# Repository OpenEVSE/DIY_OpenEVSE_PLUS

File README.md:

# DIY_OpenEVSE_PLUS
Do it Yourself through hole boards

Do it yourself boards are for expert builders, no offical support is provided.

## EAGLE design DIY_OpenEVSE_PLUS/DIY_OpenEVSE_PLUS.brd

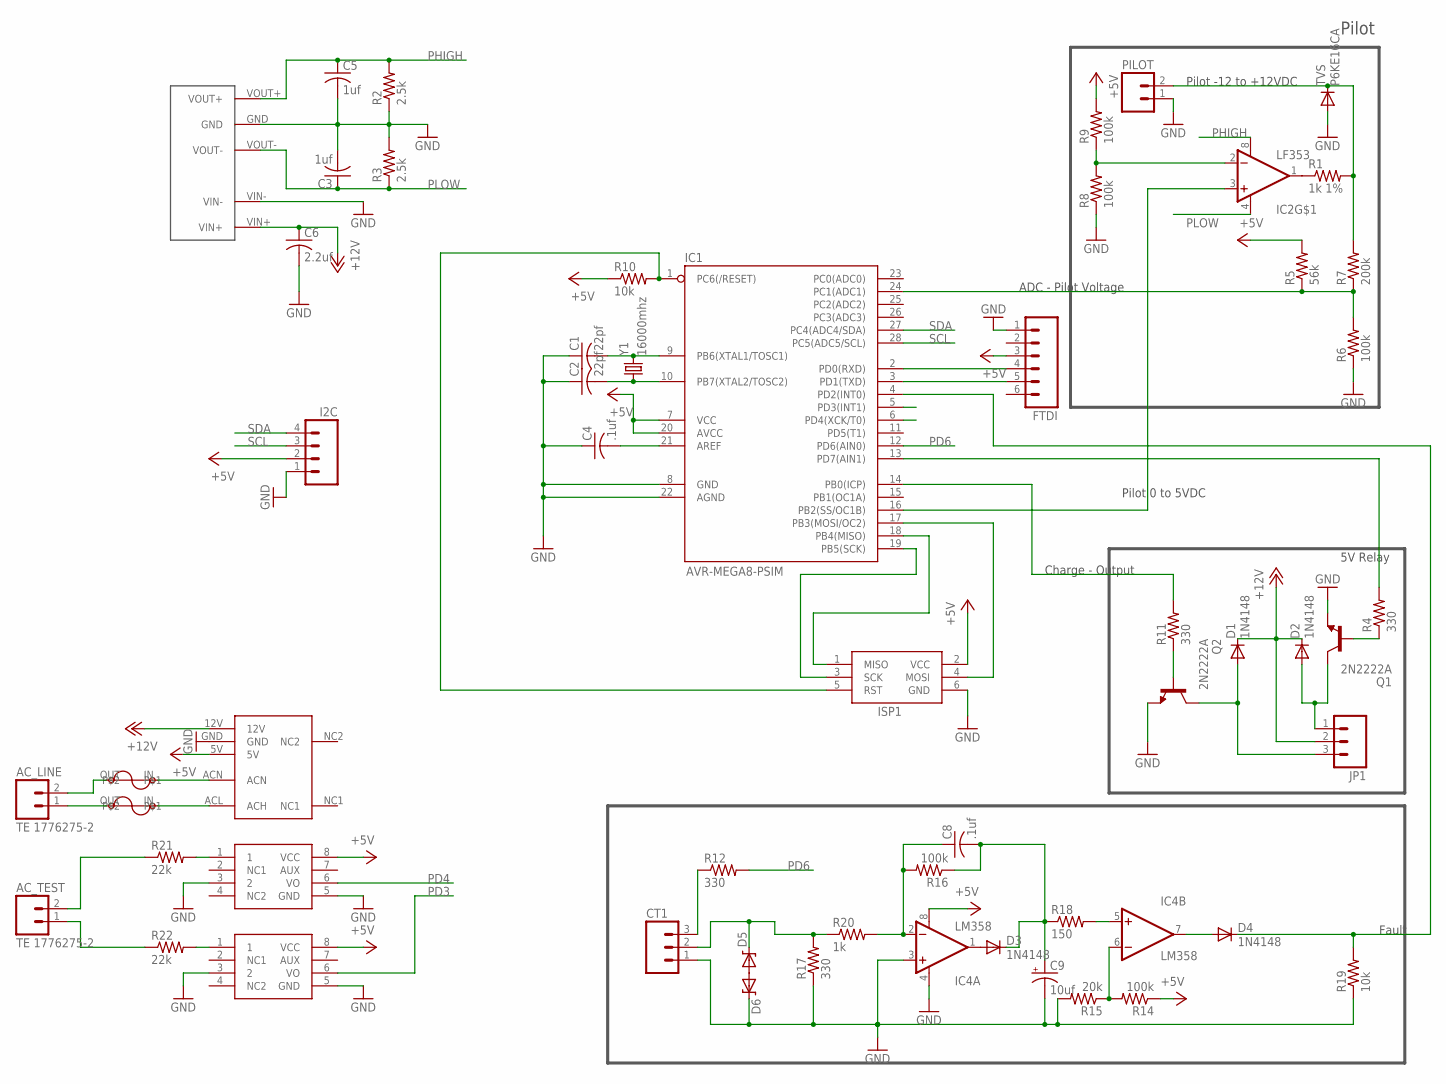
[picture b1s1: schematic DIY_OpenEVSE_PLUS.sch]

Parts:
AC_LINE: TE 1776275-2; SCREWTERMINAL-3.5MM-2_LOCK
AC_TEST: TE 1776275-2; SCREWTERMINAL-3.5MM-2_LOCK
C1, C2: 22pf; C025-024X044
C3, C5: 1uf; C025-024X044
C4, C8: .1uf; C025-024X044
C6: 2.2uf; C025-024X044
C9: 10uf; CPOL-RADIAL-10UF-25V
CT1: M03LOCK; 1X03_LOCK
D1, D2, D3, D4: 1N4148; DIODE-1N4148
D5, D6: DIODE-ZENERPTH; DIODE-ZENER
DCDC: D107E; DCDC_SIP
FTDI: M06LOCK; 1X06_LOCK
I2C: M04LOCK; 1X04_LOCK
IC1: AVR-MEGA8-PSIM; DIL28-3-SIMON
IC2: LF353; DIP08
IC3, IC5: MID400; DIP08
IC4: LM358; DIP08
ISP1: AVRISP-6; AVRISP
JP1: M03SCREW_LOCK; SCREWTERMINAL-3.5MM-3_LOCK.007S
PILOT: M025MM; SCREWTERMINAL-5MM-2
Q1, Q2: 2N2222A; TO18
R1: 1k 1%; 0204/7
R2, R3: 2.5k; 0204/7
R4, R11, R12, R17: 330; 0204/7
R5: 56k; 0204/7
R6, R8, R9, R14, R16: 100k; 0204/7
R7: 200k; 0204/7
R10, R19: 10k; 0204/7
R15: 20k; 0204/7
R18: 150; 0204/7
R20: 1k; 0204/7
R21, R22: 22k; AXIAL-0.4
TVS: P6KE16CA; DIODE-1N4001
U$3, U$5: BEL1AFUSE; BELFUSE1A
U$4: MPM-04E-1205
Y1: 16000mhz; HC49U-V

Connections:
+5V: FTDI.3, I2C.2, IC1.7 (VCC), IC1.20 (AVCC), IC3.8 (VCC), IC4.8 (V+), IC5.8 (VCC), ISP1.2 (VCC), R5.2, R9.2, R10.1, R14.1, U$4.5V
+12V: C6.1, D1.C, D2.C, DCDC.VIN+, JP1.2, U$4.12V
GND: C1.1, C2.1, C3.2, C4.1, C5.2, C6.2, C9.2 (-), CT1.1, D6.P$1 (C), DCDC.GND, DCDC.VIN-, FTDI.1, I2C.1, IC1.8 (GND), IC1.22 (AGND), IC3.3 (2), IC3.5 (GND), IC4.3 (+IN), IC4.4 (V-), IC5.3 (2), IC5.5 (GND), ISP1.6 (GND), PILOT.1, Q1.1 (E), Q2.1 (E), R2.1, R3.2, R6.1, R8.1, R15.2, R17.1, R19.1, TVS.A, U$4.GND
unnamed: AC_LINE.1, U$3.OUT
unnamed: Q2.2 (B), R11.1
unnamed: PILOT.2, R1.2, R7.2, TVS.C
unnamed: C1.2, IC1.9 (PB6(XTAL1/TOSC1)), Y1.2
unnamed: C2.2, IC1.10 (PB7(XTAL2/TOSC2)), Y1.1
unnamed: AC_LINE.2, U$5.OUT
unnamed: C4.2, IC1.21 (AREF)
unnamed: FTDI.5, IC1.3 (PD1(TXD))
unnamed: IC3.1, R21.P$2 (2)
unnamed: IC2.2 (-IN), R8.2, R9.1
unnamed: IC2.1 (OUT), R1.1
unnamed: FTDI.4, IC1.2 (PD0(RXD))
unnamed: D1.A, JP1.3, Q2.3 (C)
unnamed: IC1.17 (PB3(MOSI/OC2)), ISP1.4 (MOSI)
unnamed: IC1.19 (PB5(SCK)), ISP1.3 (SCK)
unnamed: IC1.18 (PB4(MISO)), ISP1.1 (MISO)
unnamed: IC5.1, R22.P$2 (2)
unnamed: C8.1, IC4.2 (-IN), R16.2, R20.2
unnamed: IC4.5 (+IN), R18.2
unnamed: CT1.2, D5.P$1 (C), R17.2, R20.1
unnamed: D3.A, IC4.1 (OUT)
unnamed: D5.P$2 (A), D6.P$2 (A)
unnamed: C8.2, C9.1 (+), D3.C, R16.1, R18.1
unnamed: IC4.6 (-IN), R14.2, R15.1
unnamed: D4.A, IC4.7 (OUT)
unnamed: AC_TEST.2, R21.P$1 (1)
unnamed: U$3.IN, U$4.ACL (ACH)
unnamed: D4.C, IC1.4 (PD2(INT0)), R19.2
unnamed: AC_TEST.1, R22.P$1 (1)
unnamed: U$4.ACN, U$5.IN
unnamed: Q1.2 (B), R4.1
unnamed: D2.A, JP1.1, Q1.3 (C)
unnamed: IC1.13 (PD7(AIN1)), R4.2
unnamed: IC1.14 (PB0(ICP)), R11.2
unnamed: CT1.3, R12.1
unnamed: IC1.24 (PC1(ADC1)), R5.1, R6.2, R7.1
PD3: IC1.5 (PD3(INT1)), IC5.6 (VO)
PD4: IC1.6 (PD4(XCK/T0)), IC3.6 (VO)
PD6: IC1.12 (PD6(AIN0)), R12.2
PHIGH: C5.1, DCDC.VOUT+, IC2.8 (V+), R2.2
PLOW: C3.1, DCDC.VOUT-, IC2.4 (V-), R3.1
RST: IC1.1 (PC6(/RESET)), ISP1.5 (RST), R10.2
S$2: IC1.16 (PB2(SS/OC1B)), IC2.3 (+IN)
SCL: I2C.3, IC1.28 (PC5(ADC5/SCL))
SDA: I2C.4, IC1.27 (PC4(ADC4/SDA))

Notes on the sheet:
Pilot
ADC - Pilot Voltage
Pilot -12 to +12VDC
Pilot 0 to 5VDC
Charge - Output
5V Relay
Fault

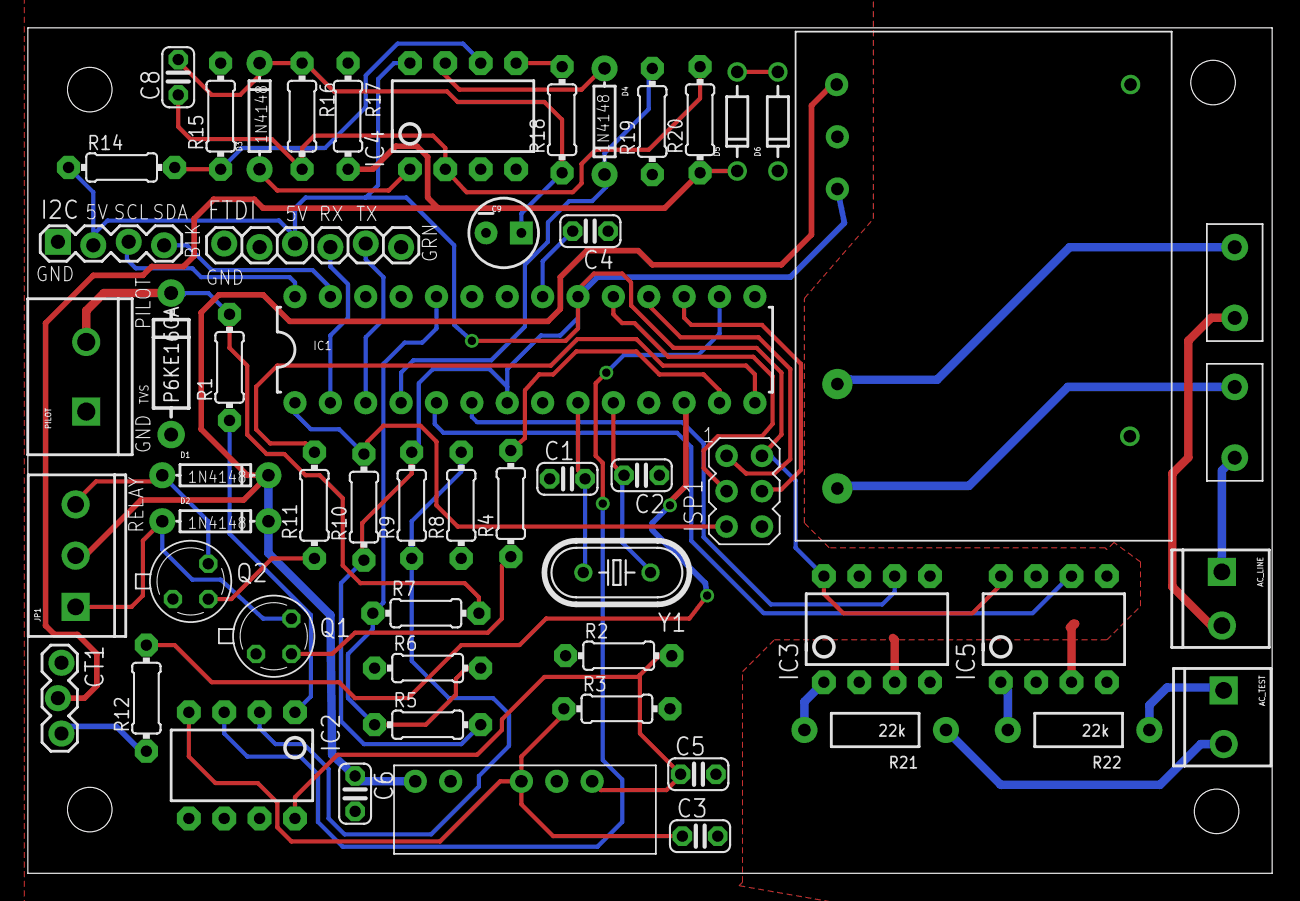
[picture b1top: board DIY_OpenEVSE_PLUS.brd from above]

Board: 2 copper layers, 89.3 x 60.7 mm, 56 parts (0 on the bottom side), 48 nets.

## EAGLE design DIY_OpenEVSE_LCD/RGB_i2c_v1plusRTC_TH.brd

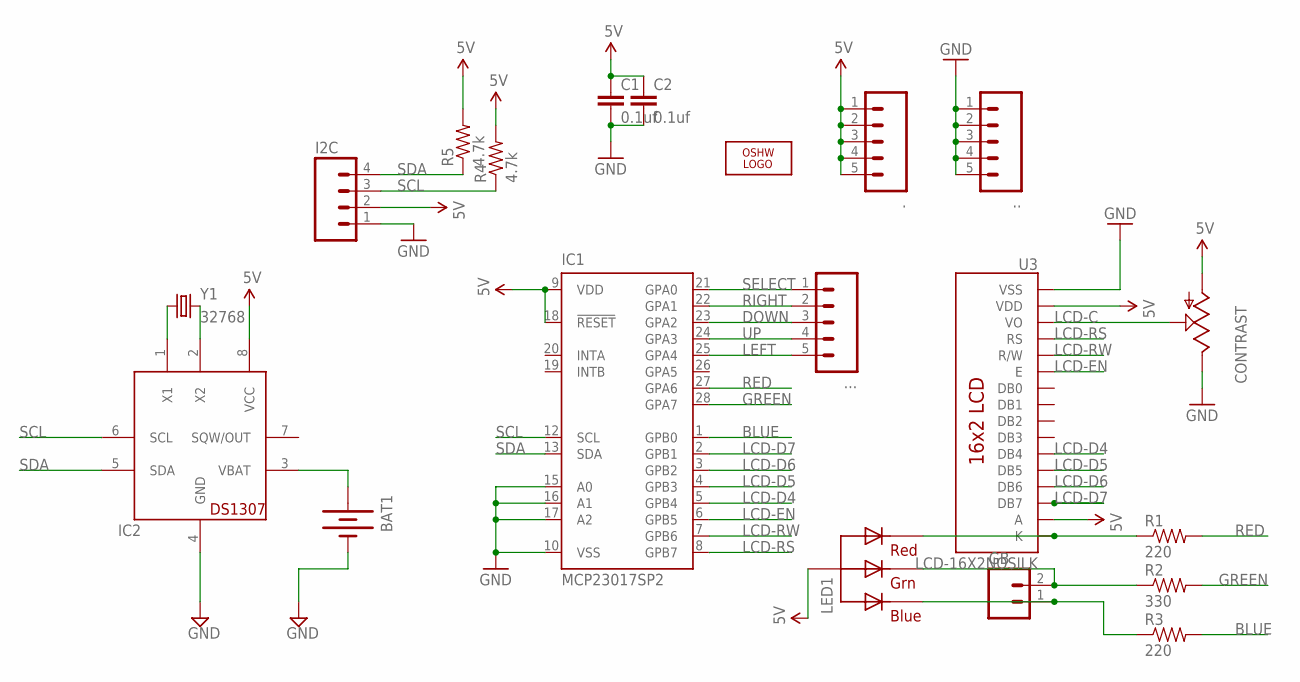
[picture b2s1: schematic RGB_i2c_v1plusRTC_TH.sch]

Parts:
., .., ...: M05LOCK; 1X05_LOCK
BAT1: BATTERY12MM; BATTCON_12MM
C1, C2: 0.1uf; CAP-PTH-SMALL-KIT
CONTRAST: TRIM; 6MM
GB: M02LOCK; 1X02_LOCK
I2C: M04LOCK; 1X04_LOCK
IC1: MCP23017SP2; DIL28-3-ROUND
IC2: DS1307; DIL08
LED1: RGBLED_CA-5MM; LED5MMRGB
LOGO2: OSHW_LOGO_10MILX0350-NT; OSHW_10X350_NOTEXT
R1, R3: 220; AXIAL-0.3
R2: 330; AXIAL-0.3
R4, R5: 4.7k; AXIAL-0.3
U3: LCD-16X2NOSILK; LCD-16X2_NOSILK
Y1: 32768; TC38H

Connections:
5V: ..1, ..2, ..3, ..4, ..5, C1.1, C2.1, CONTRAST.A, I2C.2, IC1.9 (VDD), IC1.18 (!RESET), IC2.8 (VCC), LED1.2 (VCC), R4.P$2 (2), R5.P$2 (2), U3.2 (VDD), U3.15 (A)
BLUE: IC1.1 (GPB0), R3.P$2 (2)
DOWN: ....3, IC1.23 (GPA2)
GND: ...1, ...2, ...3, ...4, ...5, BAT1.GND (-), C1.2, C2.2, CONTRAST.E, I2C.1, IC1.10 (VSS), IC1.15 (A0), IC1.16 (A1), IC1.17 (A2), IC2.4 (GND), U3.1 (VSS)
GREEN: IC1.28 (GPA7), R2.P$2 (2)
LCD-C: CONTRAST.S, U3.3 (VO)
LCD-D4: IC1.5 (GPB4), U3.11 (DB4)
LCD-D5: IC1.4 (GPB3), U3.12 (DB5)
LCD-D6: IC1.3 (GPB2), U3.13 (DB6)
LCD-D7: IC1.2 (GPB1), U3.14 (DB7)
LCD-EN: IC1.6 (GPB5), U3.6 (E)
LCD-RS: IC1.8 (GPB7), U3.4 (RS)
LCD-RW: IC1.7 (GPB6), U3.5 (R/W)
LEFT: ....5, IC1.25 (GPA4)
unnamed: GB.2, LED1.3 (GREEN), R2.P$1 (1)
unnamed: GB.1, LED1.4 (BLUE), R3.P$1 (1)
unnamed: BAT1.PWR@1 (+), IC2.3 (VBAT)
unnamed: LED1.1 (RED), R1.P$1 (1), U3.16 (K)
unnamed: IC2.1 (X1), Y1.1
unnamed: IC2.2 (X2), Y1.2
RED: IC1.27 (GPA6), R1.P$2 (2)
RIGHT: ....2, IC1.22 (GPA1)
SCL: I2C.3, IC1.12 (SCL), IC2.6 (SCL), R4.P$1 (1)
SDA: I2C.4, IC1.13 (SDA), IC2.5 (SDA), R5.P$1 (1)
SELECT: ....1, IC1.21 (GPA0)
UP: ....4, IC1.24 (GPA3)

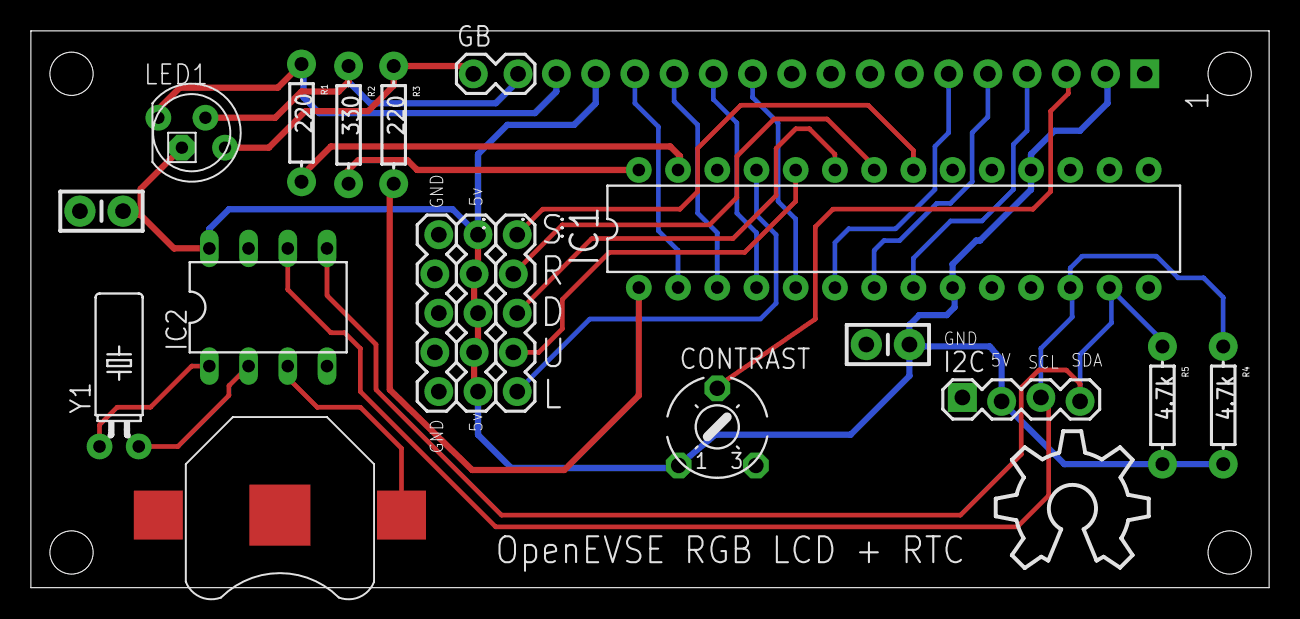
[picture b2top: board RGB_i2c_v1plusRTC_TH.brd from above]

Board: 2 copper layers, 80.2 x 36.1 mm, 20 parts (1 on the bottom side), 26 nets.

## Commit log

2015-10-09 :space_invader: Added .gitattributes & .gitignore files
2015-10-09 DIY OpenEVSE PLUS
    Do it Yourself versions of OpenEVSE boards. All Through Hole Parts.
2015-10-09 Added DIY LCD
2015-10-09 DIY OpenEVSE Arduino Shield
    DIY OpenEVSE Arduino Shield
2017-05-10 some airwire problems fix.
